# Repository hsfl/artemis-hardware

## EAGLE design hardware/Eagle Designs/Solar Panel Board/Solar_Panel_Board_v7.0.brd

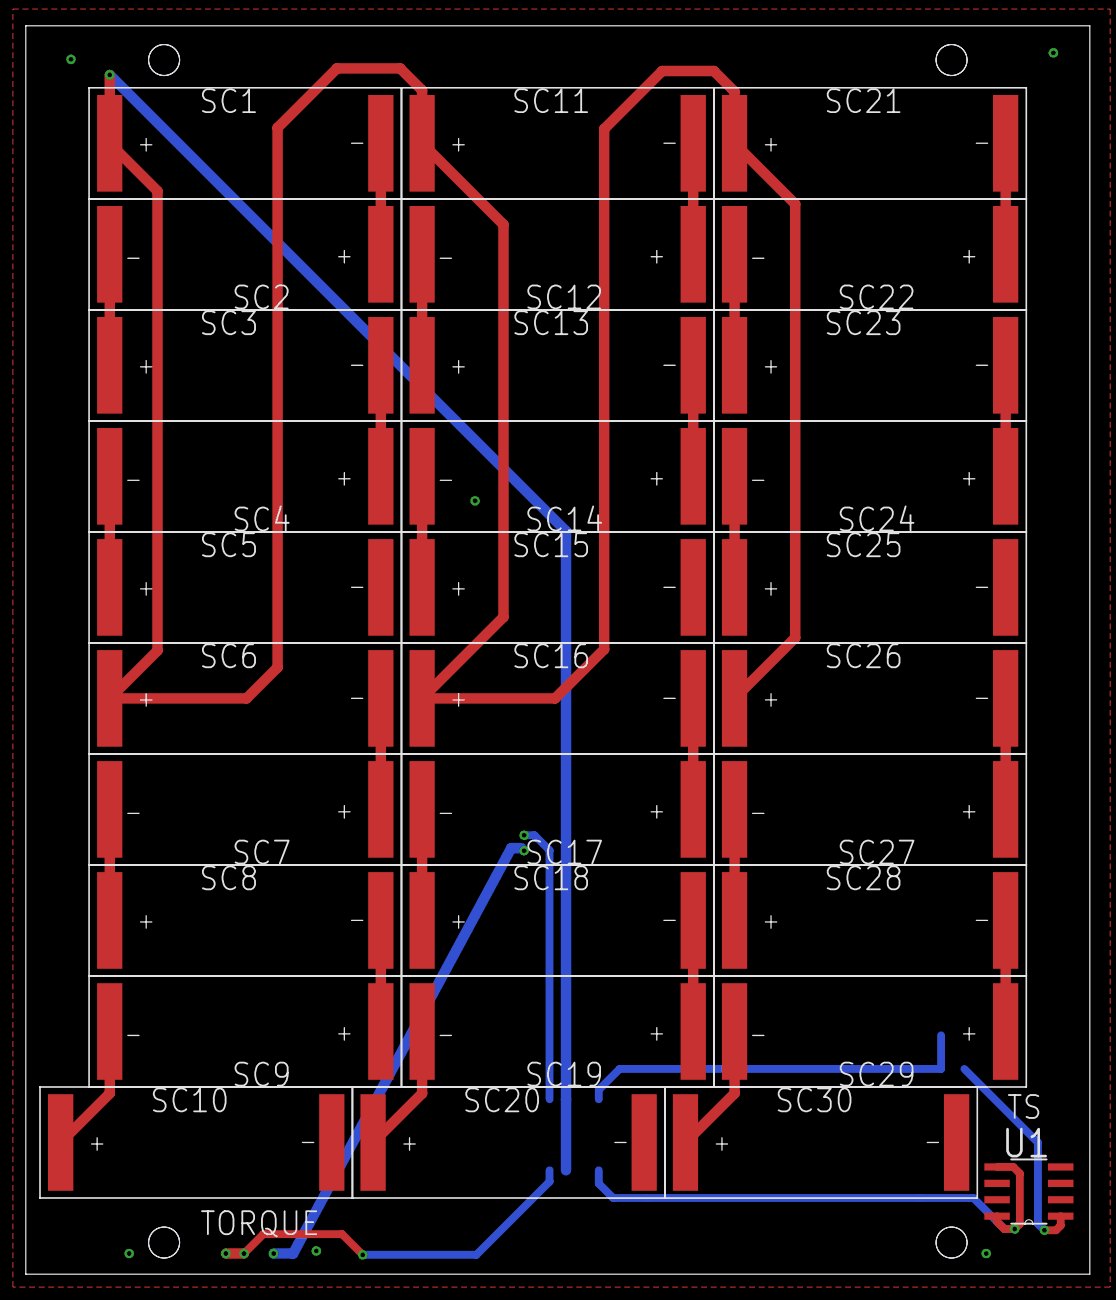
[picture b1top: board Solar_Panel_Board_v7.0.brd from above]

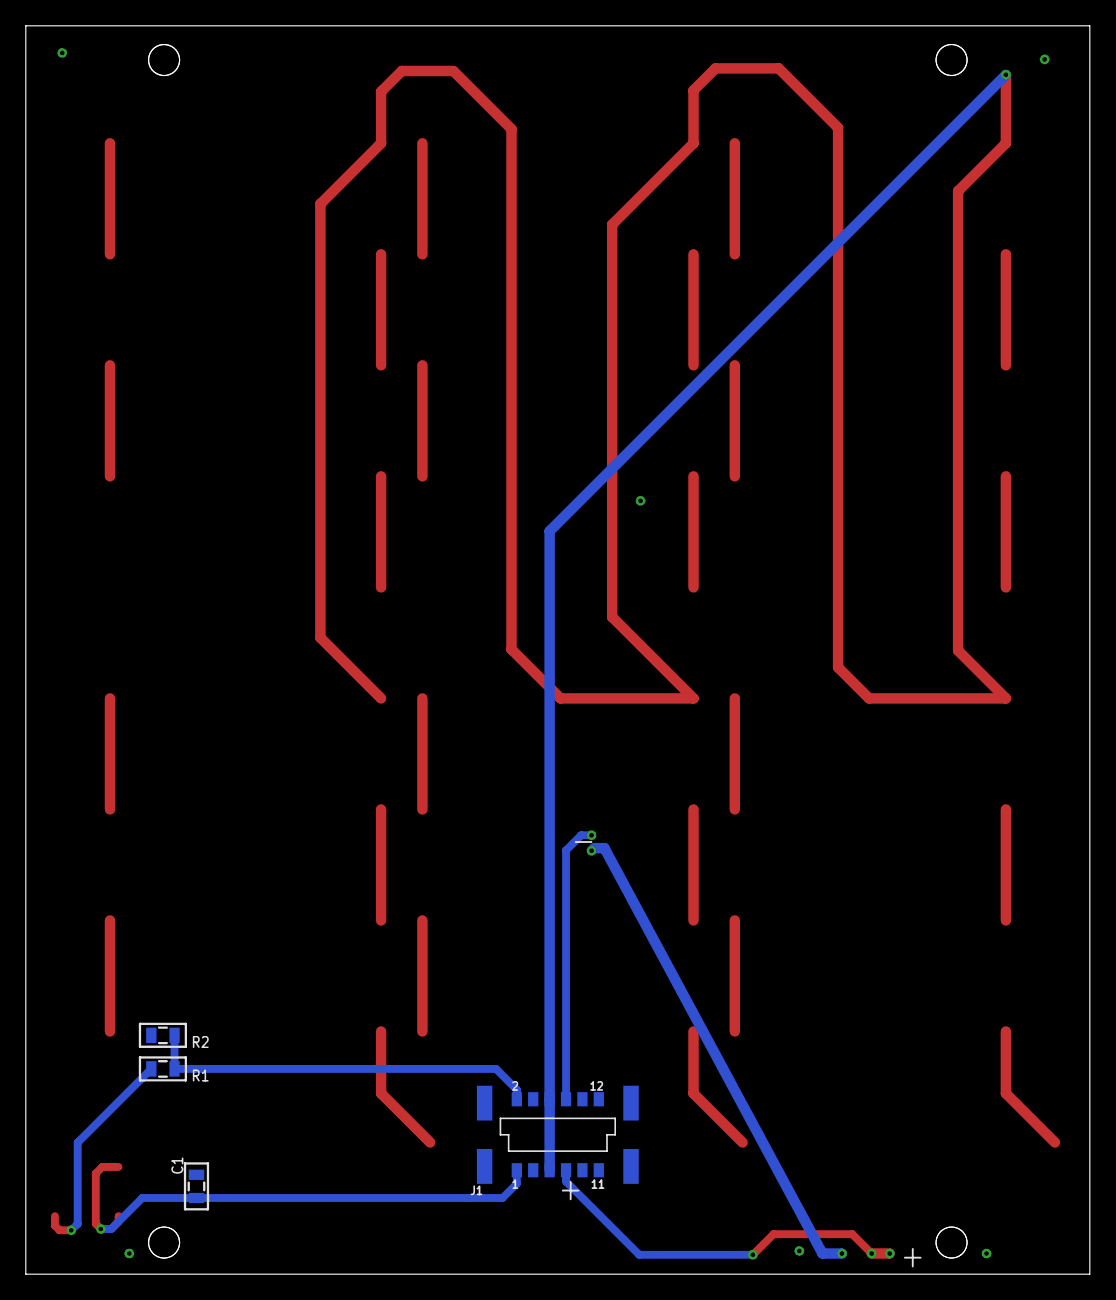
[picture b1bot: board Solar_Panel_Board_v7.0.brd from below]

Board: 4 copper layers, 82.4 x 96.7 mm, 35 parts (4 on the bottom side), 30 nets.

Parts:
C1: 0.1uF; 0805
J1: M55-6021242R
R1: 45.3k; 0805
R2: 10k; 0805
SC1, SC2, SC3, SC4, SC5, SC6, SC7, SC8, SC9, SC10, SC11, SC12, SC13, SC14, SC15, SC16, SC17, SC18, SC19, SC20, SC21, SC22, SC23, SC24, SC25, SC26, SC27, SC28, SC29, SC30: KXOB25-05X3F
U1: TMP36GSZ; SOIC127P600X175-8N

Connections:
GND: C1.2, J1.3, J1.4, J1.P$1, J1.P$2, J1.P$3, J1.P$4, R2.1, SC5.-, SC10.-, SC15.-, SC20.-, SC25.-, SC30.-, U1.4
unnamed: J1.7, J1.8
unnamed: SC7.-, SC8.+
unnamed: SC4.-, SC5.+
unnamed: SC3.-, SC4.+
unnamed: SC2.-, SC3.+
unnamed: SC1.-, SC2.+
unnamed: SC8.-, SC9.+
unnamed: SC16.-, SC17.+
unnamed: SC14.-, SC15.+
unnamed: SC13.-, SC14.+
unnamed: SC9.-, SC10.+
unnamed: R1.2, U1.1
unnamed: SC11.-, SC12.+
unnamed: SC23.-, SC24.+
unnamed: SC22.-, SC23.+
unnamed: SC21.-, SC22.+
unnamed: SC6.-, SC7.+
unnamed: SC17.-, SC18.+
unnamed: SC19.-, SC20.+
unnamed: SC12.-, SC13.+
unnamed: SC28.-, SC29.+
unnamed: SC29.-, SC30.+
unnamed: SC26.-, SC27.+
unnamed: SC24.-, SC25.+
unnamed: SC18.-, SC19.+
unnamed: SC27.-, SC28.+
VCC: J1.5, J1.6, SC1.+, SC6.+, SC11.+, SC16.+, SC21.+, SC26.+
VOUT: J1.2, R1.1, R2.2
VS+: C1.1, J1.1, U1.5, U1.8

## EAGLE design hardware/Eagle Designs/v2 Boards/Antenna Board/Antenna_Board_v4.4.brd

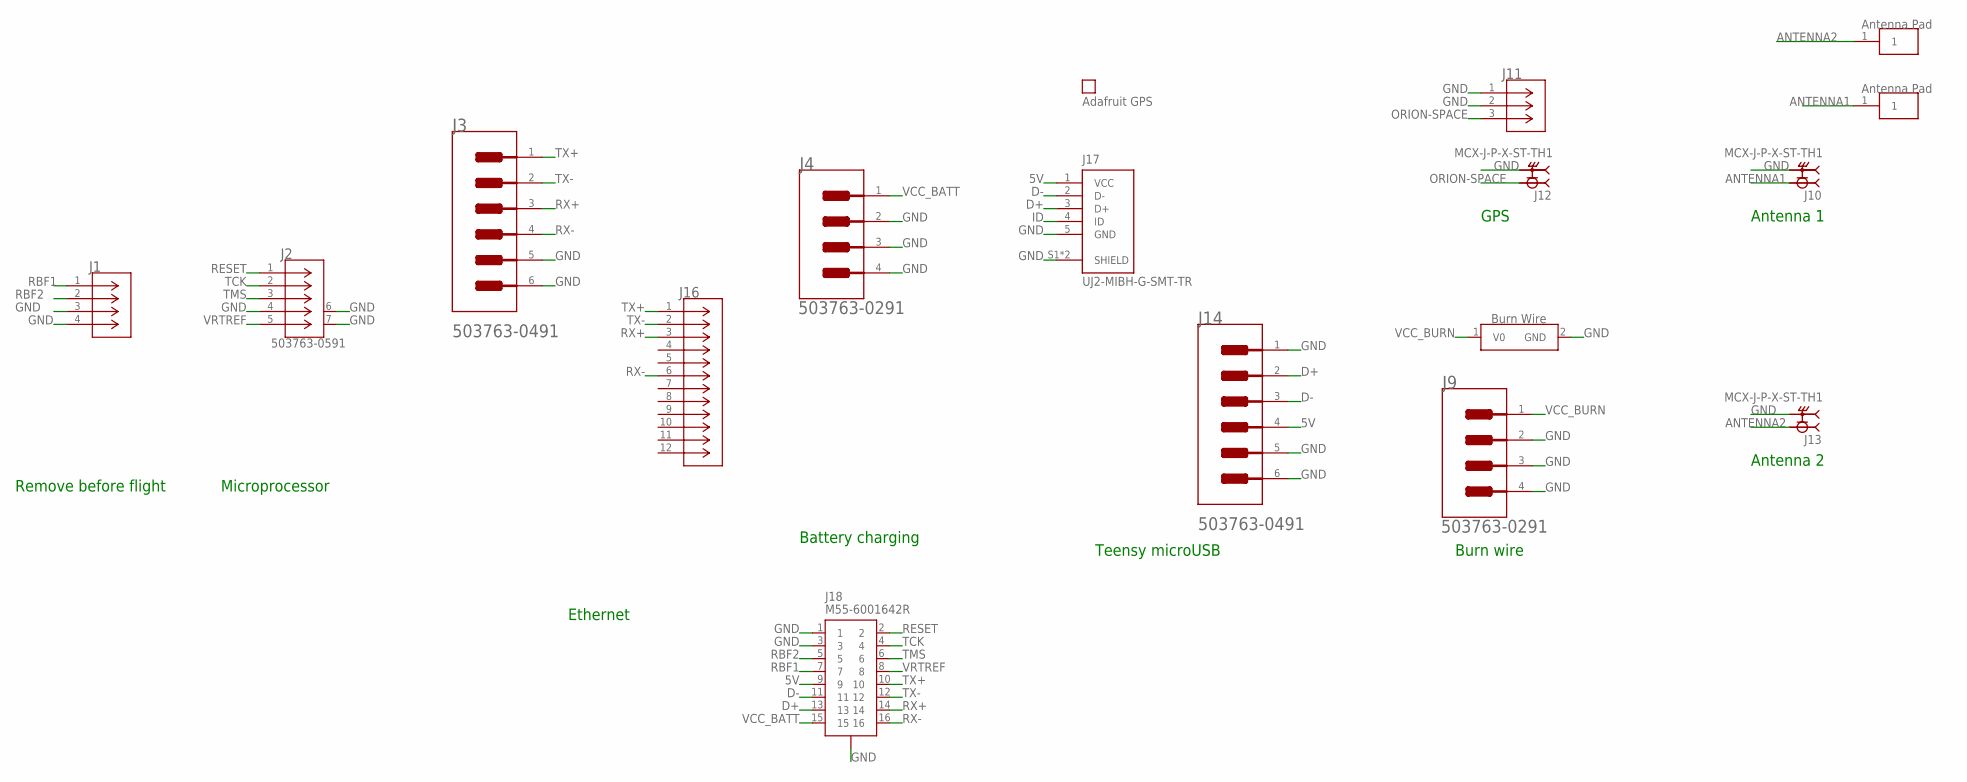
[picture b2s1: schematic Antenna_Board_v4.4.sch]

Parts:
GPS: PA1010D
J1: 5037630291; CON_5037630291
J2: 503763-0591; CONN_5037630591_MOL
J3, J14: MOLEX_503763-0491MOLEX_503763-0491_0_0; MOLEX_503763-0491_0
J4, J9: MOLEX_503763-0291MOLEX_503763-0291_0_0; MOLEX_503763-0291_0
J10, J12, J13: MCX-J-P-X-ST-TH1; SAMTEC_MCX-J-P-X-ST-TH1
J11: U.FL-R-SMT-1(01); CONN_-SMT-1(01)
J16: ARJM11C7-104-AB-EW2; CONN_EW_ABR
J17: UJ2-MIBH-G-SMT-TR; CUI_UJ2-MIBH-G-SMT-TR
J18: M55-6001642R; CONN_M55-6001642R_HRW
U$1, U$2: ANTENNA_PAD
U$3: BURNWIRE

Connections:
5V: J14.4, J17.1 (VCC), J18.9
ANTENNA1: J10.1, U$2.1
ANTENNA2: J13.1, U$1.1
D+: J14.2, J17.3 (D+), J18.13
D-: J14.3, J17.2 (D-), J18.11
GND: J1.3, J1.4, J2.4, J2.6, J2.7, J3.5 (MNT_1), J3.6 (MNT_2), J4.2, J4.3 (MNT_1), J4.4 (MNT_2), J9.2, J9.3 (MNT_1), J9.4 (MNT_2), J10.S1 (2), J10.S2 (2), J10.S3 (2), J10.S4 (2), J11.1, J11.2, J12.S1 (2), J12.S2 (2), J12.S3 (2), J12.S4 (2), J13.S1 (2), J13.S2 (2), J13.S3 (2), J13.S4 (2), J14.1, J14.5 (MNT_1), J14.6 (MNT_2), J17.5 (GND), J17.S1 (SHIELD), J17.S2 (SHIELD), J18.1, J18.3, J18.19 (17), J18.20 (17), J18.21 (17), J18.22 (17), U$3.2 (GND)
ID: J17.4 (ID)
ORION-SPACE: J11.3, J12.1
RBF1: J1.1, J18.7
RBF2: J1.2, J18.5
RESET: J2.1, J18.2
RX+: J3.3, J16.3, J18.14
RX-: J3.4, J16.6, J18.16
TCK: J2.2, J18.4
TMS: J2.3, J18.6
TX+: J3.1, J16.1, J18.10
TX-: J3.2, J16.2, J18.12
VCC_BATT: J4.1, J18.15
VCC_BURN: J9.1, U$3.1 (V0)
VRTREF: J2.5, J18.8

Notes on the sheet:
Remove before flight
Microprocessor
Battery charging
Teensy microUSB
Burn wire
GPS
Antenna 1
Antenna 2
Ethernet

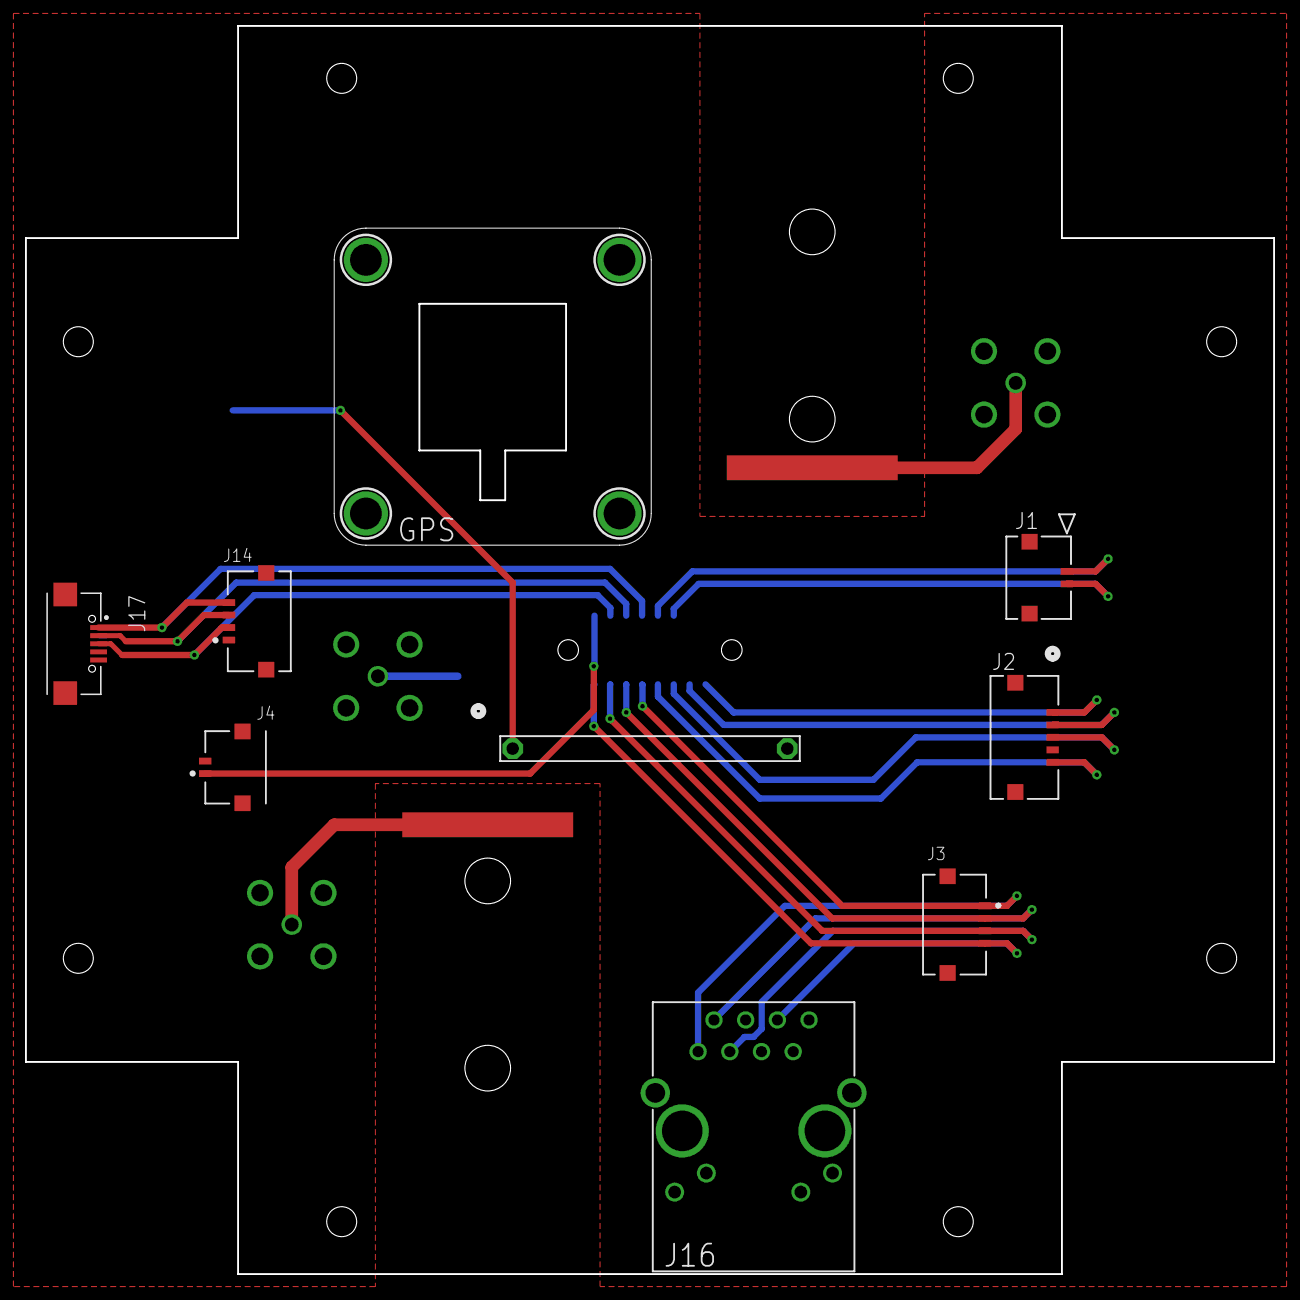
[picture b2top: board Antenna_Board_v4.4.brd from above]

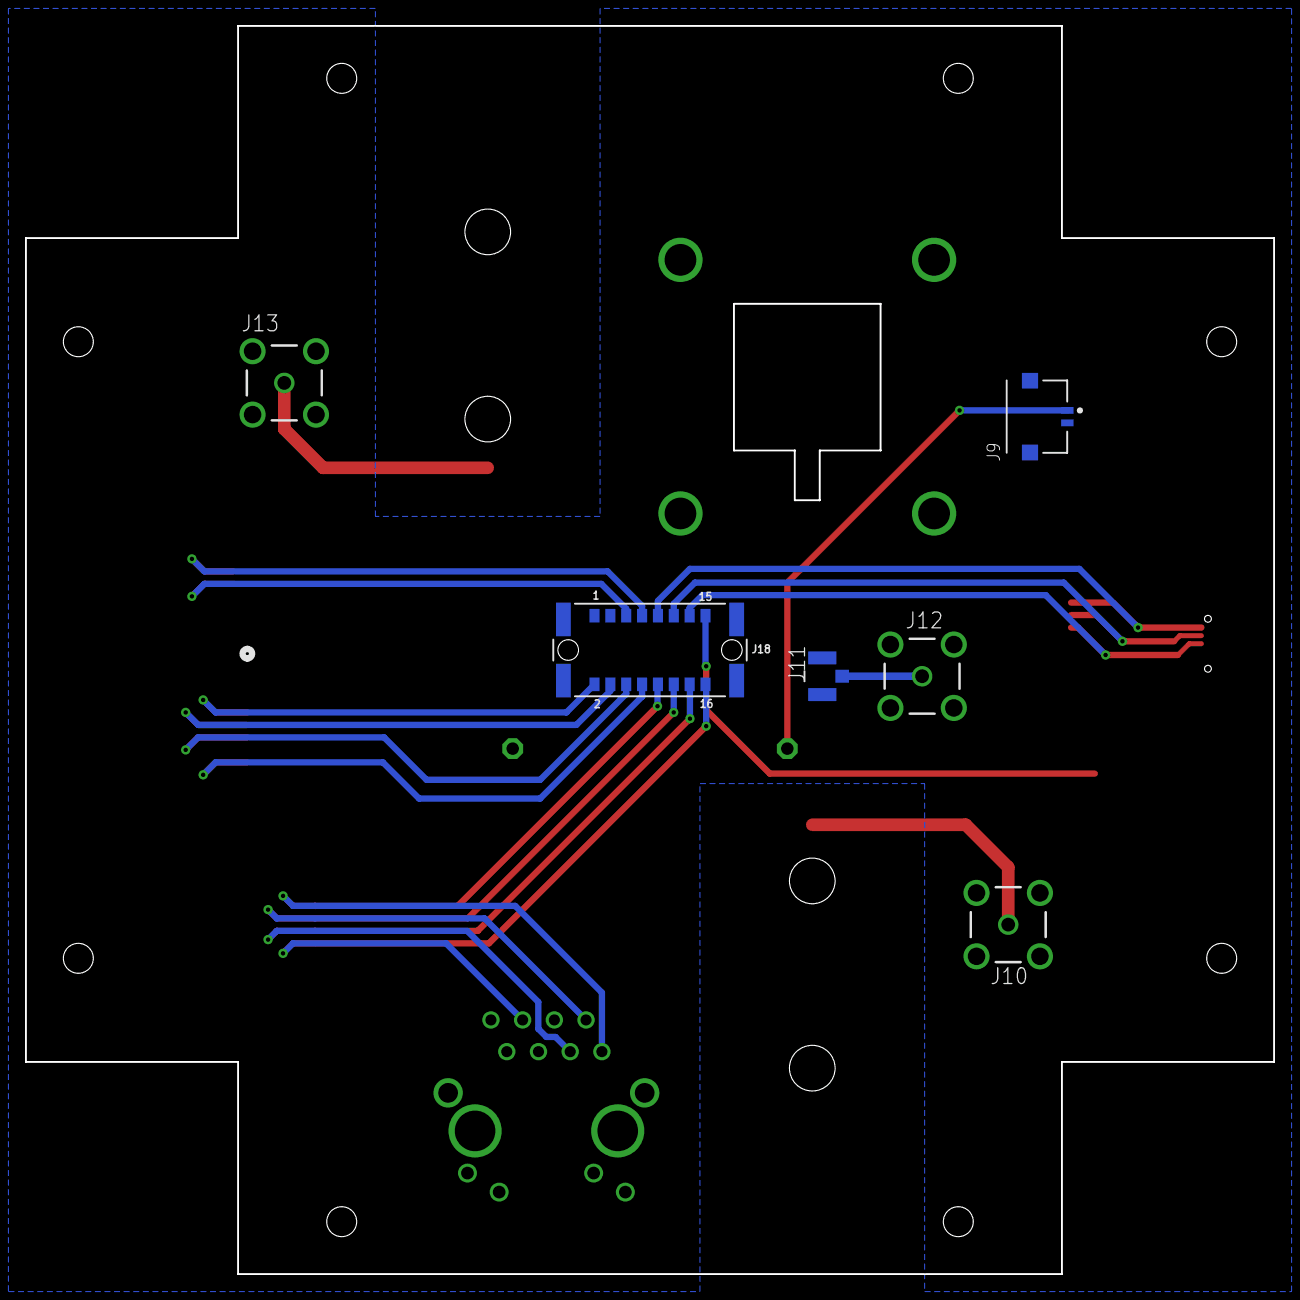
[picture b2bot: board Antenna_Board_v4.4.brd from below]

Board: 2 copper layers, 100.0 x 100.0 mm, 17 parts (6 on the bottom side), 19 nets.

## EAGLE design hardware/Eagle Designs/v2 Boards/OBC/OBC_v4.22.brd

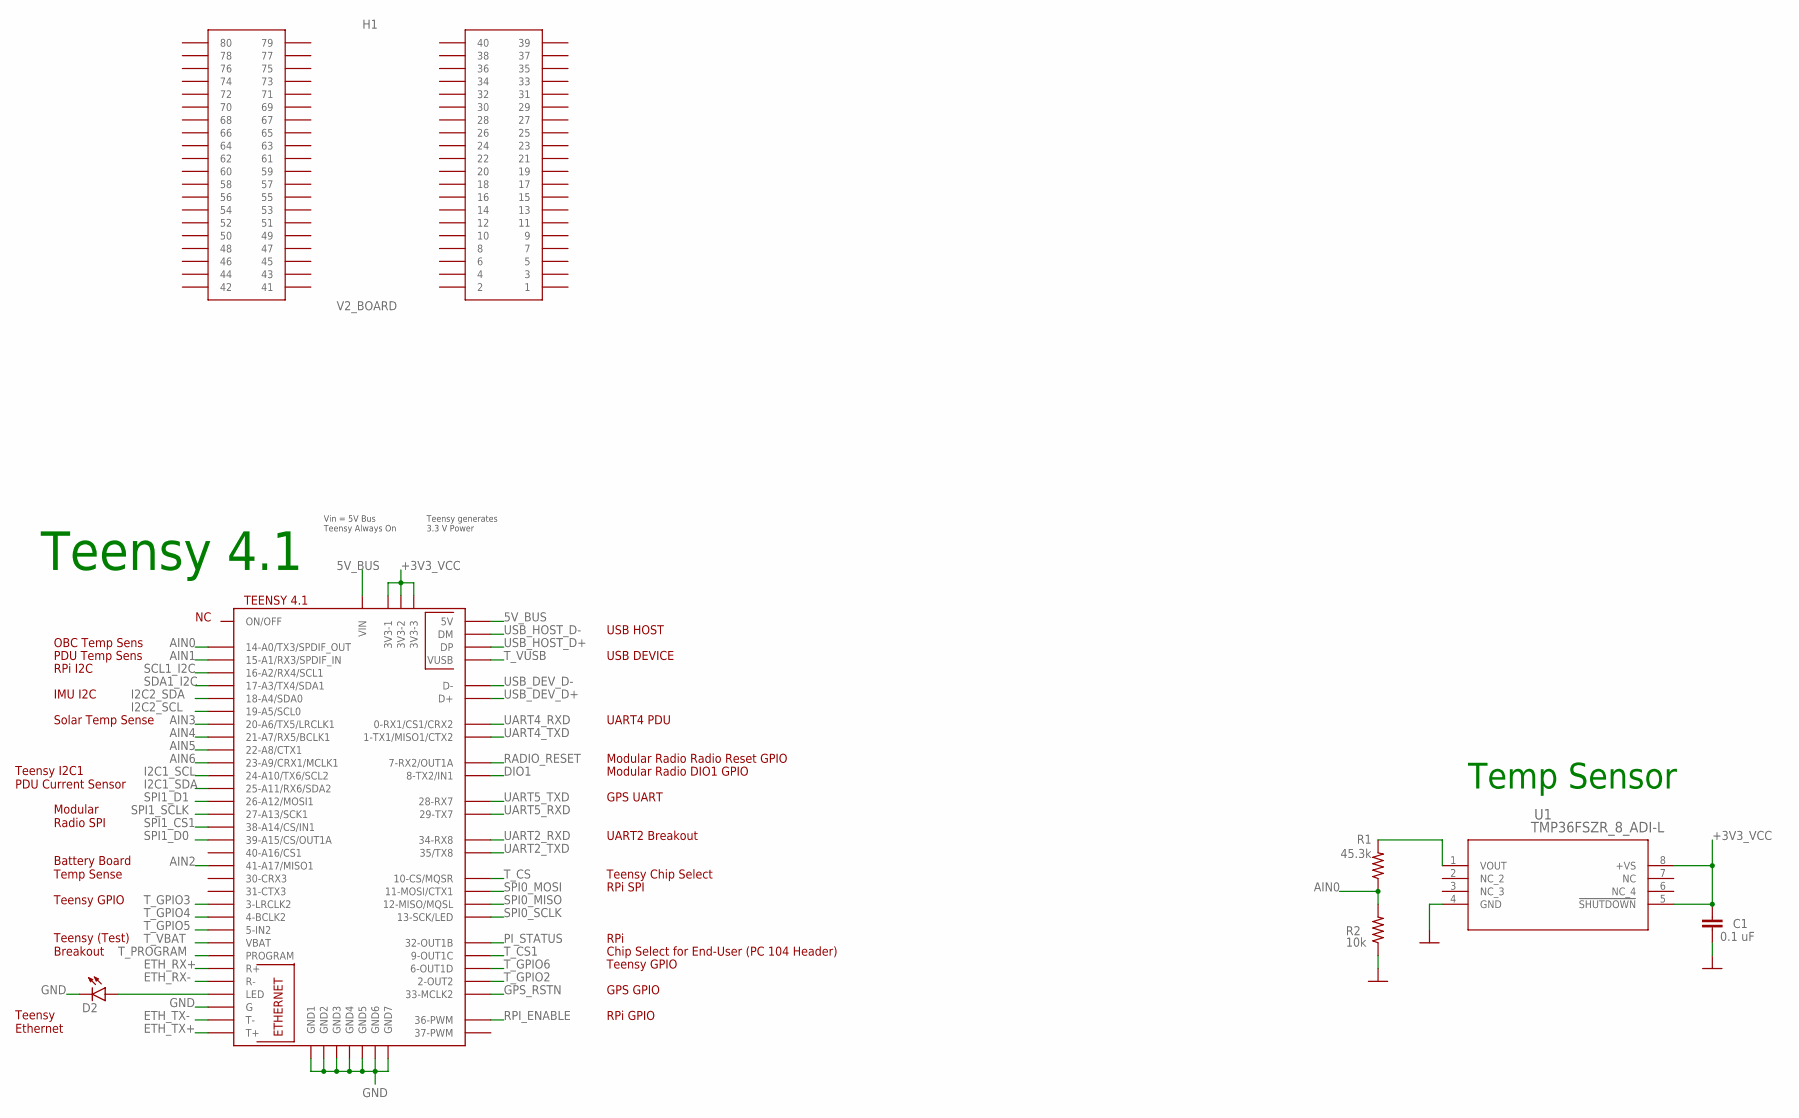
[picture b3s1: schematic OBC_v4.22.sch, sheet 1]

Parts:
C1: 0.1 uF; 0805
D2: LEDCHIP-LED0603; CHIP-LED0603
H1: V2_BOARD; BOARD_TEMPLATE
R1: 45.3k; 0805
R2: 10k; 0805
U1: TMP36FSZR_8_ADI-L; R_8_ADI-L
U$1: TEENSY41TEENSY; TEENSY41

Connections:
5V_BUS: U$1.+5V (5V), U$1.VIN; also elsewhere on the board
+3V3_VCC: C1.1, U1.5 (!SHUTDOWN), U1.8 (+VS), U$1.3V3-1, U$1.3V3-2, U$1.3V3-3; also elsewhere on the board
AIN0: R1.1, R2.2, U$1.14-A0/TX3/SPDIF_OUT
AIN1: U$1.15-A1/RX3/SPDIF_IN
AIN2: U$1.41-A17/MISO1
AIN3: U$1.20-A6/TX5/LRCLK1
AIN4: U$1.21-A7/RX5/BCLK1
AIN5: U$1.22-A8/CTX1
AIN6: U$1.23-A9/CRX1/MCLK1
DIO1: U$1.8-TX2/IN1; also elsewhere on the board
ETH_RX+: U$1.R+
ETH_RX-: U$1.R-
ETH_TX+: U$1.T+
ETH_TX-: U$1.T-
GND: C1.2, D2.C, R2.1, U1.4 (GND), U$1.G, U$1.GND (GND7), U$1.GND1, U$1.GND2, U$1.GND3, U$1.GND4, U$1.GND5, U$1.GND6; also elsewhere on the board
GPS_RSTN: U$1.33-MCLK2; also elsewhere on the board
I2C1_SCL: U$1.24-A10/TX6/SCL2
I2C1_SDA: U$1.25-A11/RX6/SDA2
I2C2_SCL: U$1.19-A5/SCL0; also elsewhere on the board
I2C2_SDA: U$1.18-A4/SDA0; also elsewhere on the board
unnamed: D2.A, U$1.LED
unnamed: R1.2, U1.1 (VOUT)
PI_STATUS: U$1.32-OUT1B; also elsewhere on the board
RADIO_RESET: U$1.7-RX2/OUT1A; also elsewhere on the board
RPI_ENABLE: U$1.36-PWM; also elsewhere on the board
SCL1_I2C: U$1.16-A2/RX4/SCL1; also elsewhere on the board
SDA1_I2C: U$1.17-A3/TX4/SDA1; also elsewhere on the board
SPI0_MISO: U$1.12-MISO/MQSL; also elsewhere on the board
SPI0_MOSI: U$1.11-MOSI/CTX1; also elsewhere on the board
SPI0_SCLK: U$1.13-SCK/LED; also elsewhere on the board
SPI1_CS1: U$1.38-A14/CS/IN1; also elsewhere on the board
SPI1_D0: U$1.39-A15/CS/OUT1A; also elsewhere on the board
SPI1_D1: U$1.26-A12/MOSI1; also elsewhere on the board
SPI1_SCLK: U$1.27-A13/SCK1; also elsewhere on the board
T_CS: U$1.10-CS\MQSR (10-CS/MQSR)
T_CS1: U$1.9-OUT1C
T_GPIO2: U$1.2-OUT2
T_GPIO3: U$1.3-LRCLK2
T_GPIO4: U$1.4-BCLK2
T_GPIO5: U$1.5-IN2
T_GPIO6: U$1.6-OUT1D
T_PROGRAM: U$1.PROGRAM
T_VBAT: U$1.VBAT
T_VUSB: U$1.VUSB
UART2_RXD: U$1.34-RX8
UART2_TXD: U$1.35-TX8 (35/TX8)
UART4_RXD: U$1.0-RX1/CS1/CRX2
UART4_TXD: U$1.1-TX1/MISO1/CTX2
UART5_RXD: U$1.29-TX7; also elsewhere on the board
UART5_TXD: U$1.28-RX7; also elsewhere on the board
USB_DEV_D+: U$1.D+
USB_DEV_D-: U$1.D-
USB_HOST_D+: U$1.DP
USB_HOST_D-: U$1.DM

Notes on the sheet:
Temp Sensor
Teensy 4.1
OBC Temp Sens
PDU Temp Sens
RPi I2C
IMU I2C
Solar Temp Sense
Teensy I2C1 PDU Current Sensor
Modular Radio SPI
Battery Board Temp Sense
Teensy GPIO
Teensy (Test) Breakout
Teensy Ethernet
RPi GPIO
GPS GPIO
RPi SPI
Teensy Chip Select
UART2 Breakout
GPS UART
Modular Radio Radio Reset GPIO
UART4 PDU
USB HOST
USB DEVICE
Vin = 5V Bus Teensy Always On
Teensy generates 3.3 V Power
Modular Radio DIO1 GPIO
Chip Select for End-User (PC 104 Header)
RPi

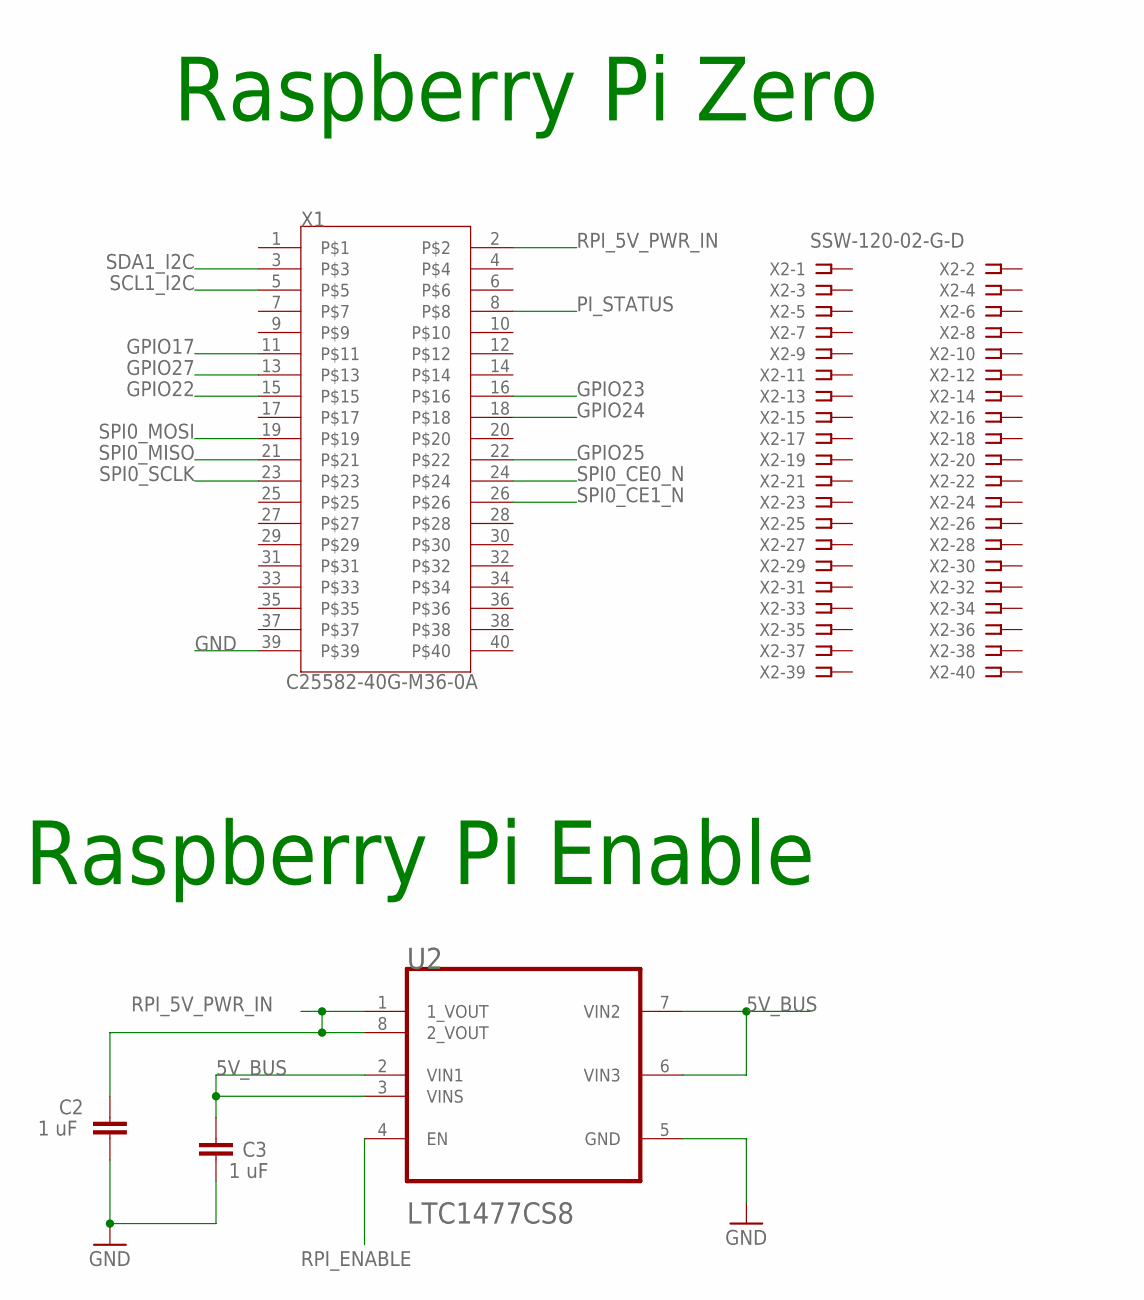
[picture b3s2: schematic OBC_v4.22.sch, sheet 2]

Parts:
C2, C3: 1 uF; 0805
U2: LTC1477CS8LINEAR_TECHNOLOGY_LTC1477CS8_0_2; LINEAR_TECHNOLOGY_LTC1477CS8_2
X1: C25582-40G-M36-0A; ADAFRUIT_C25582-40G-M36-0A_0
X2: SSW-120-02-G-D

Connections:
5V_BUS: C3.1, U2.2 (VIN1), U2.3 (VINS), U2.6 (VIN3), U2.7 (VIN2); also elsewhere on the board
GND: C2.2, C3.2, U2.5 (GND), X1.39; also elsewhere on the board
GPIO17: X1.11
GPIO22: X1.15
GPIO23: X1.16
GPIO24: X1.18
GPIO25: X1.22
GPIO27: X1.13
PI_STATUS: X1.8; also elsewhere on the board
RPI_5V_PWR_IN: C2.1, U2.1 (1_VOUT), U2.8 (2_VOUT), X1.2
RPI_ENABLE: U2.4 (EN); also elsewhere on the board
SCL1_I2C: X1.5; also elsewhere on the board
SDA1_I2C: X1.3; also elsewhere on the board
SPI0_CE0_N: X1.24
SPI0_CE1_N: X1.26
SPI0_MISO: X1.21; also elsewhere on the board
SPI0_MOSI: X1.19; also elsewhere on the board
SPI0_SCLK: X1.23; also elsewhere on the board

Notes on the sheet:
Raspberry Pi Zero
Raspberry Pi Enable

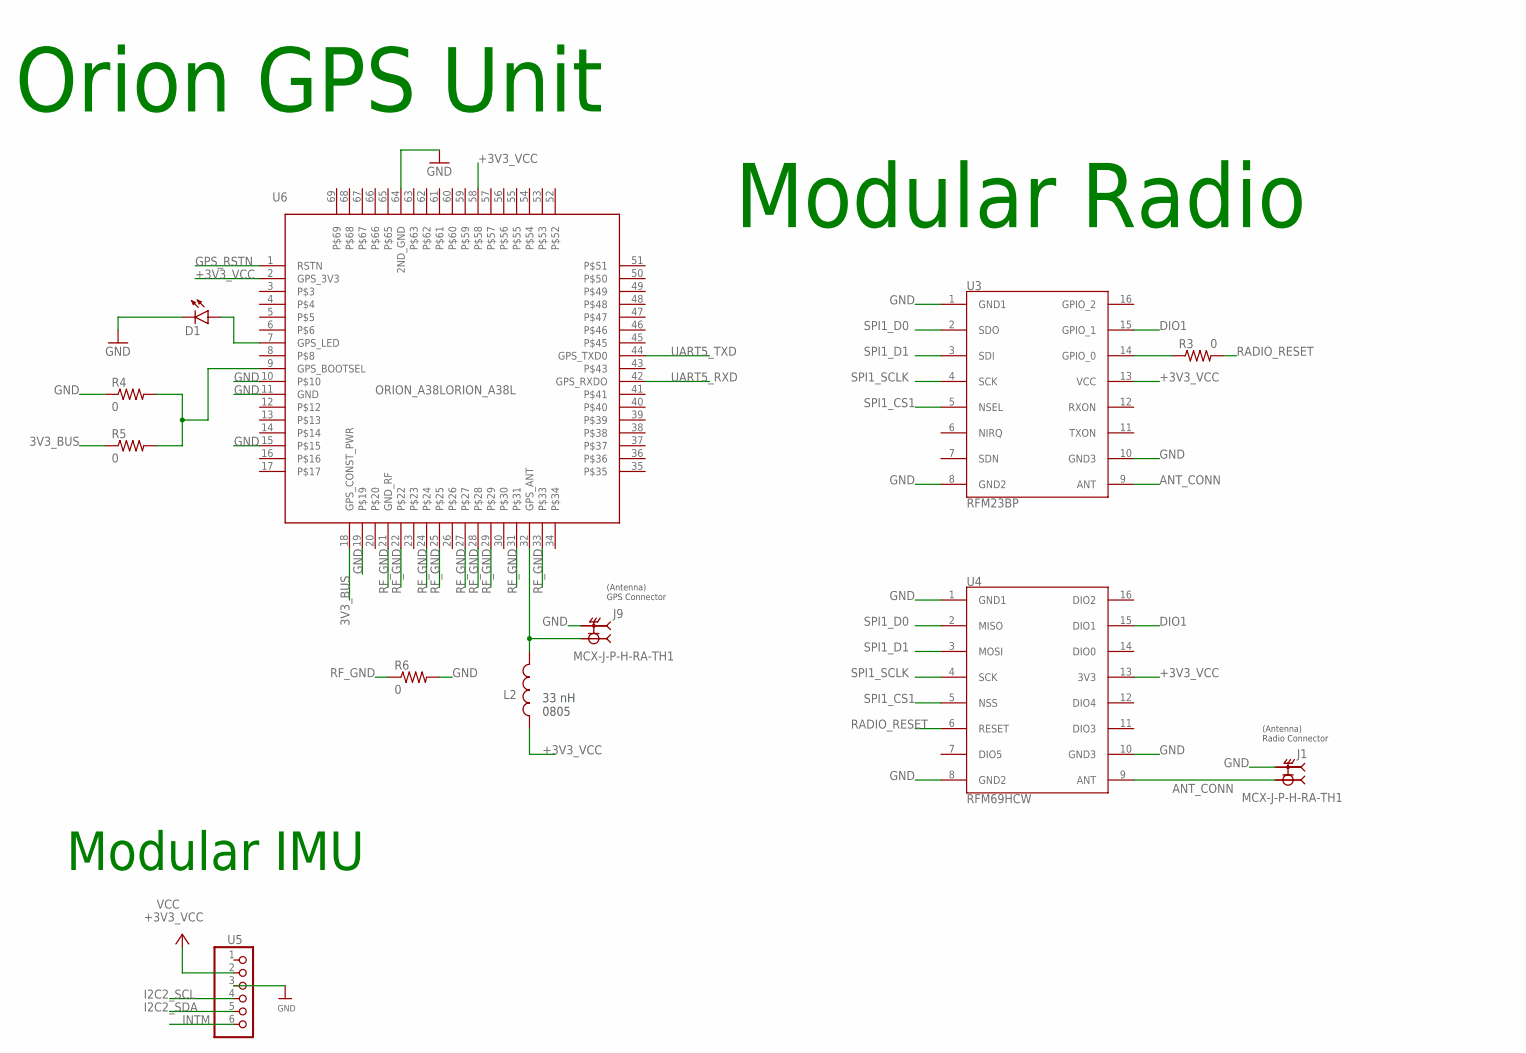
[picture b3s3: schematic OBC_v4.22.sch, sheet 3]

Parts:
D1: LEDCHIP-LED0603; CHIP-LED0603
J1, J9: MCX-J-P-H-RA-TH1; SAMTEC_MCX-J-P-H-RA-TH1
L2: AIMC-0805-2N2S-T; INDC2012X105N
R3, R4, R5, R6: 0; 0805
U3: RFM23BP
U4: RFM69HCW
U5: HEADER-1X670MIL; 1X06_ROUND_70
U6: ORION_A38LORION_A38L; ORION_A38L

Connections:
3V3_BUS: R5.1, U6.18 (GPS_CONST_PWR)
+3V3_VCC: L2.1, U3.13 (VCC), U4.13 (3V3), U5.2, U6.2 (GPS_3V3), U6.58; also elsewhere on the board
ANT_CONN: J1.1, U3.9 (ANT), U4.9 (ANT)
DIO1: U3.15 (GPIO_1), U4.15 (DIO1); also elsewhere on the board
GND: D1.C, J1.S1 (2), J1.S2 (2), J1.S3 (2), J1.S4 (2), J9.S1 (2), J9.S2 (2), J9.S3 (2), J9.S4 (2), R4.1, R6.2, U3.1 (GND1), U3.8 (GND2), U3.10 (GND3), U4.1 (GND1), U4.8 (GND2), U4.10 (GND3), U5.3, U6.10, U6.11 (GND), U6.15, U6.19, U6.64 (2ND_GND); also elsewhere on the board
GPS_RSTN: U6.1 (RSTN); also elsewhere on the board
I2C2_SCL: U5.4; also elsewhere on the board
I2C2_SDA: U5.5; also elsewhere on the board
INTM: U5.6
unnamed: R3.1, U3.14 (GPIO_0)
unnamed: R4.2, R5.2, U6.9 (GPS_BOOTSEL)
unnamed: J9.1, L2.2, U6.32 (GPS_ANT)
unnamed: D1.A, U6.7 (GPS_LED)
RADIO_RESET: R3.2, U4.6 (RESET); also elsewhere on the board
RF_GND: R6.1, U6.21 (GND_RF), U6.22, U6.24, U6.25, U6.27, U6.28, U6.29, U6.31, U6.33
SPI1_CS1: U3.5 (NSEL), U4.5 (NSS); also elsewhere on the board
SPI1_D0: U3.2 (SDO), U4.2 (MISO); also elsewhere on the board
SPI1_D1: U3.3 (SDI), U4.3 (MOSI); also elsewhere on the board
SPI1_SCLK: U3.4 (SCK), U4.4 (SCK); also elsewhere on the board
UART5_RXD: U6.42 (GPS_RXDO); also elsewhere on the board
UART5_TXD: U6.44 (GPS_TXD0); also elsewhere on the board

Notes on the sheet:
Orion GPS Unit
Modular Radio
Modular IMU
(Antenna) Radio Connector
(Antenna) GPS Connector
33 nH 0805

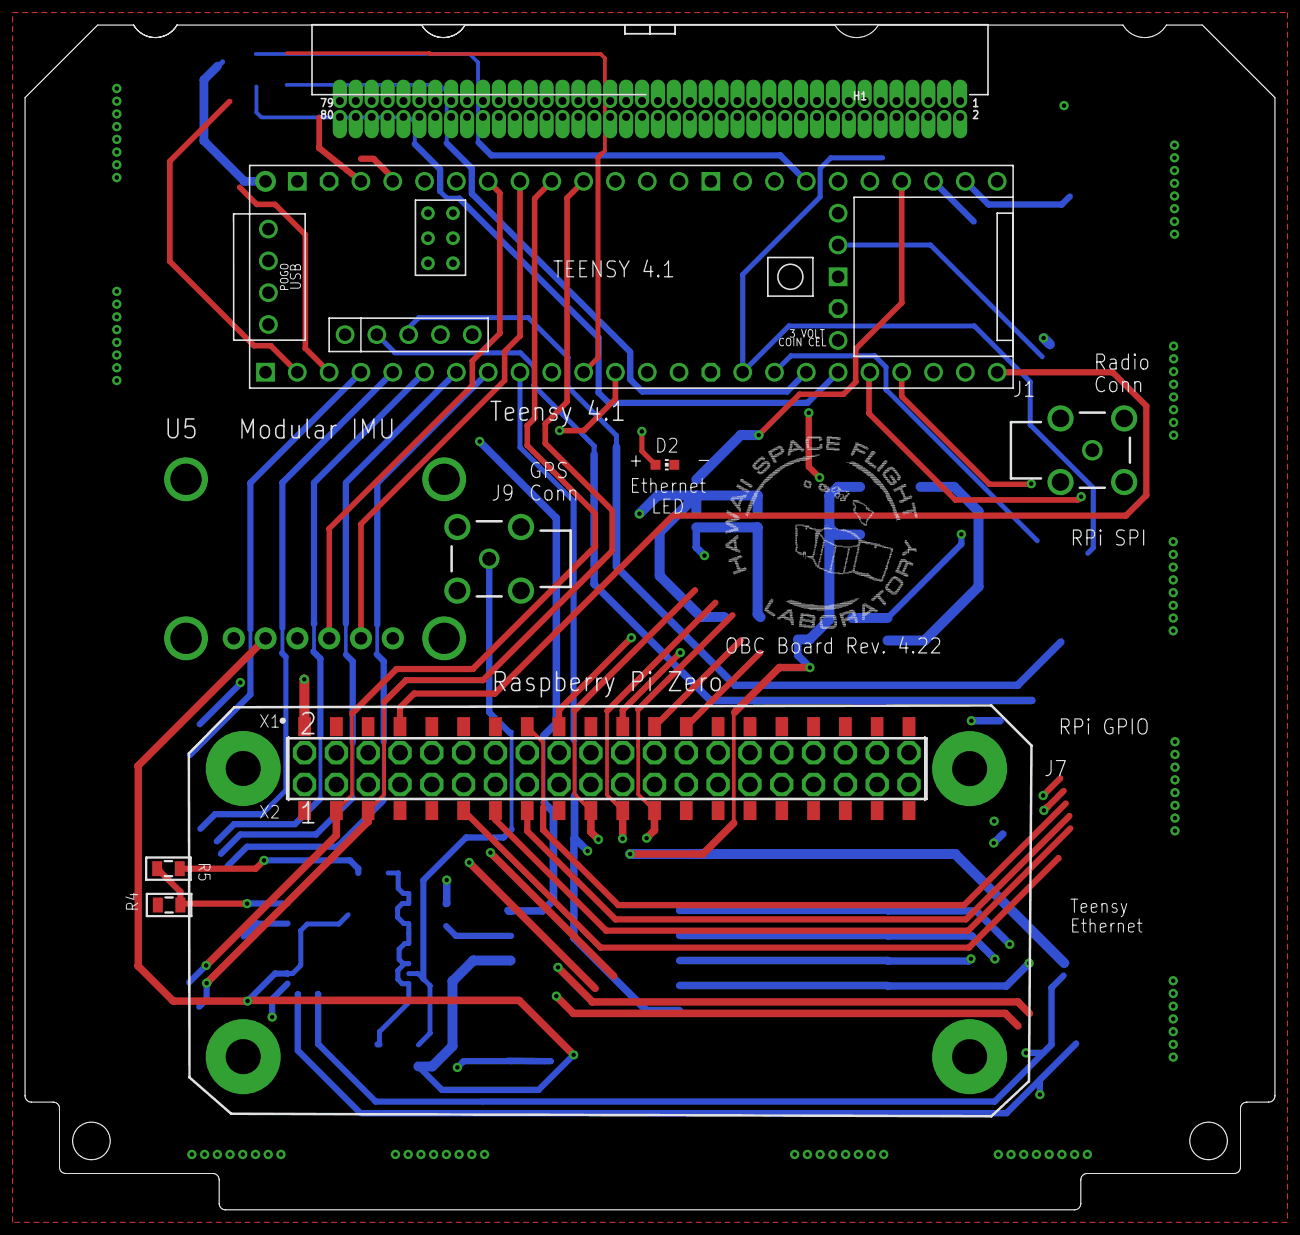
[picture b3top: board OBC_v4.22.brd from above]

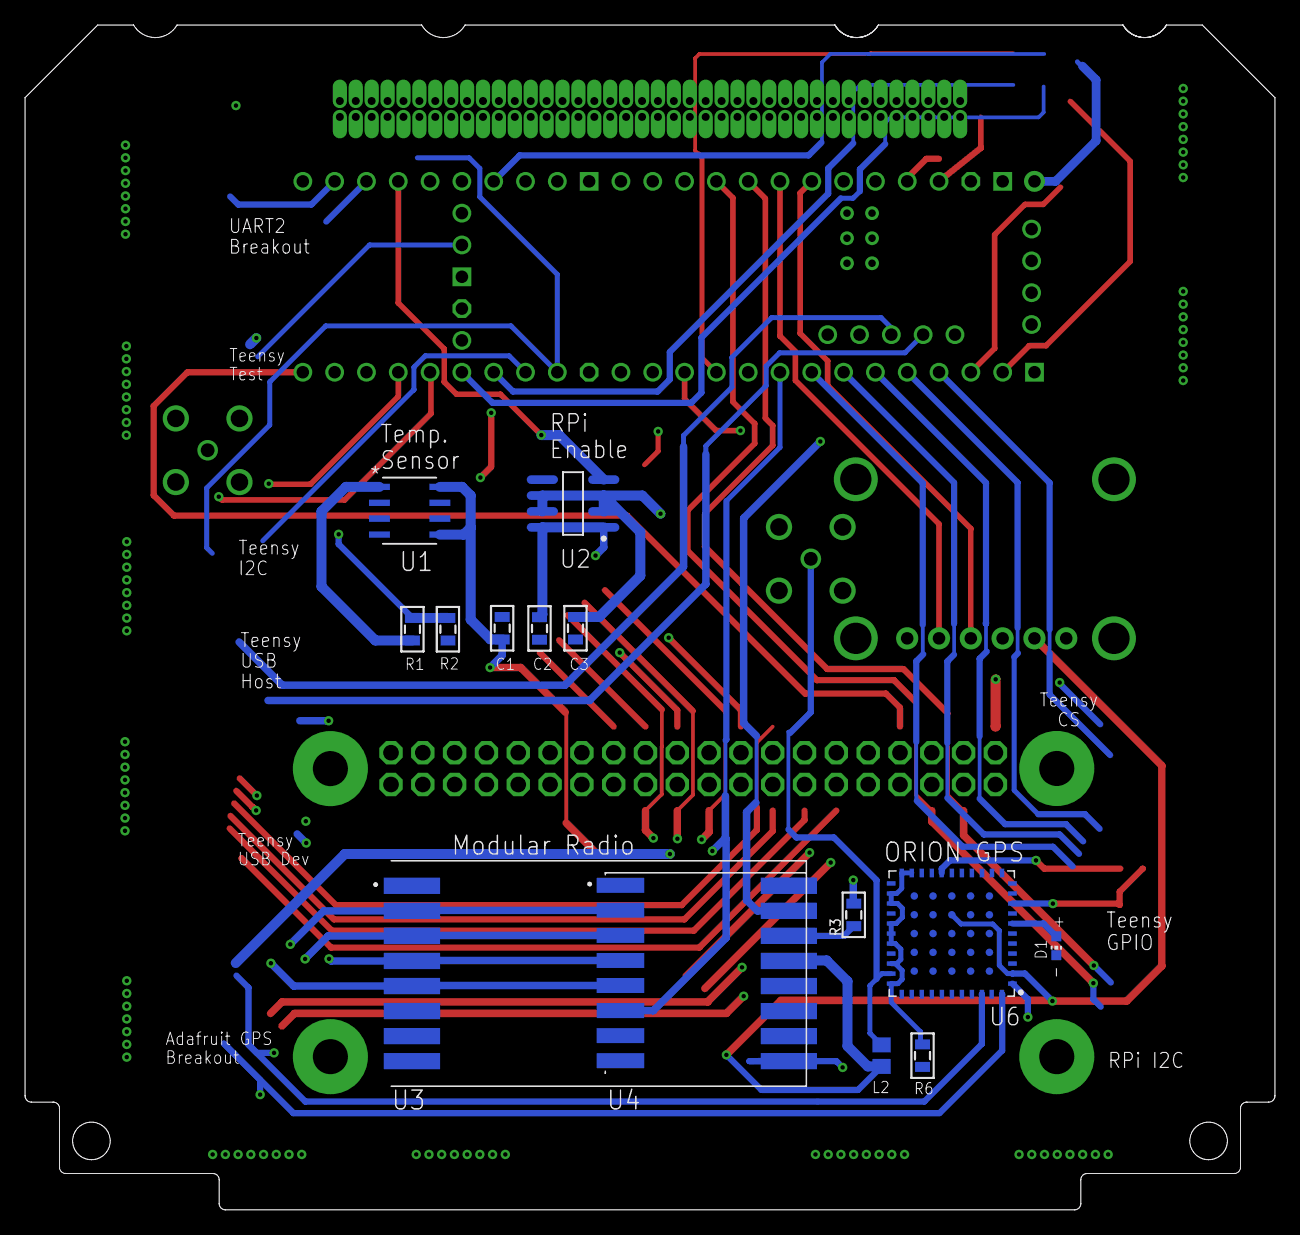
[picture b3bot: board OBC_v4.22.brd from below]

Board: 4 copper layers, 99.8 x 94.6 mm, 24 parts (14 on the bottom side), 32 nets.

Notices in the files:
parts and their libraries:
SparkFun-PowerSymbols: Licensing: Creative Commons ShareAlike 4.0 International - https://creativecommons.org/licenses/by-sa/4.0
Improved Molex 503763-0591: COPYRIGHT: Copyright (C) 2018 Accelerated Designs. All rights reserved
COPYRIGHT: Copyright (C) 2021 Ultra Librarian. All rights reserved.
